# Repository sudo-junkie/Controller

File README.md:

# Controller

KiCad 7 design files (schematic, PCB, gerber, BOM) for a replacement PCB for the UCOM USB game controller that introduces the following features:
- ESP32 based (WiFi + Bluetooth onboard) with external (IPEX) antenna
- SPI LCD Connector
- Micro SD Card slot 
- Single cell lithium battery charger
- USB C for programming/joystick
- Onboard accelerometer + gyroscope + magnetometer (MPU9250)
- 8 analog inputs (4 pressure-sensitive buttons + 2 joysticks)
- 8 digital inputs
- Toggle switch
- Infrared TX/RX 
- RGB LED

While this board has been designed to be dimensionally identical to the original PCB, a little 'hacking' on the part of the casing to make room for the USB connector, infrared transmitter/receiver and for the mounting of the toggle switch and external ESP32 antenna.

- Original

- Upgraded

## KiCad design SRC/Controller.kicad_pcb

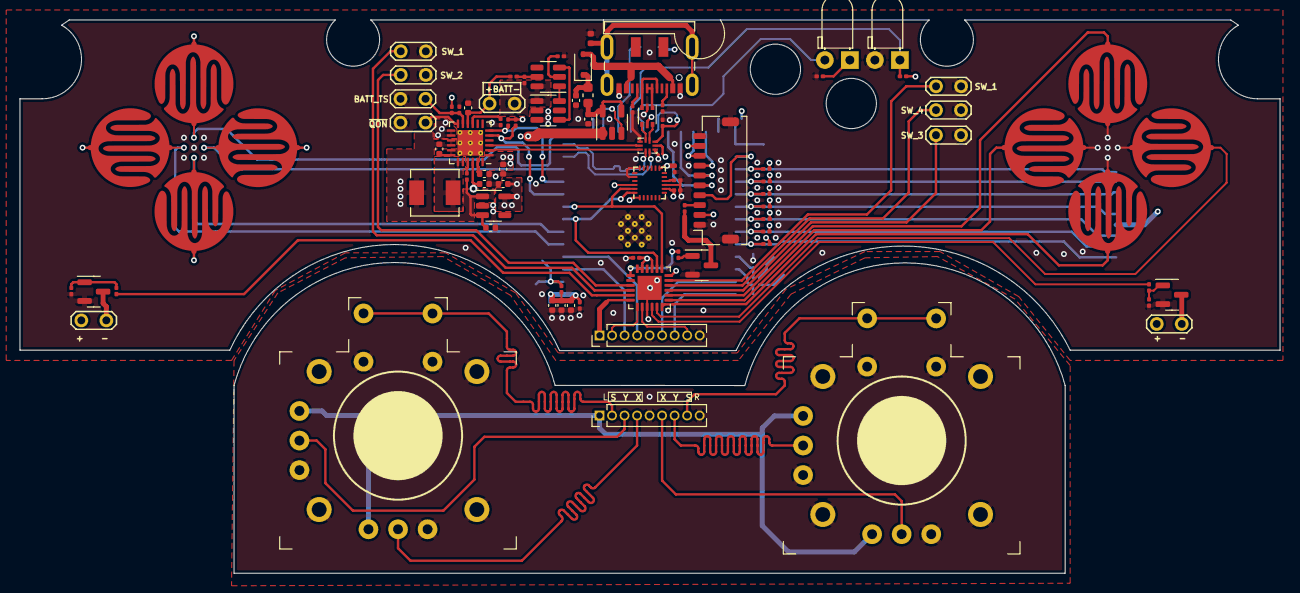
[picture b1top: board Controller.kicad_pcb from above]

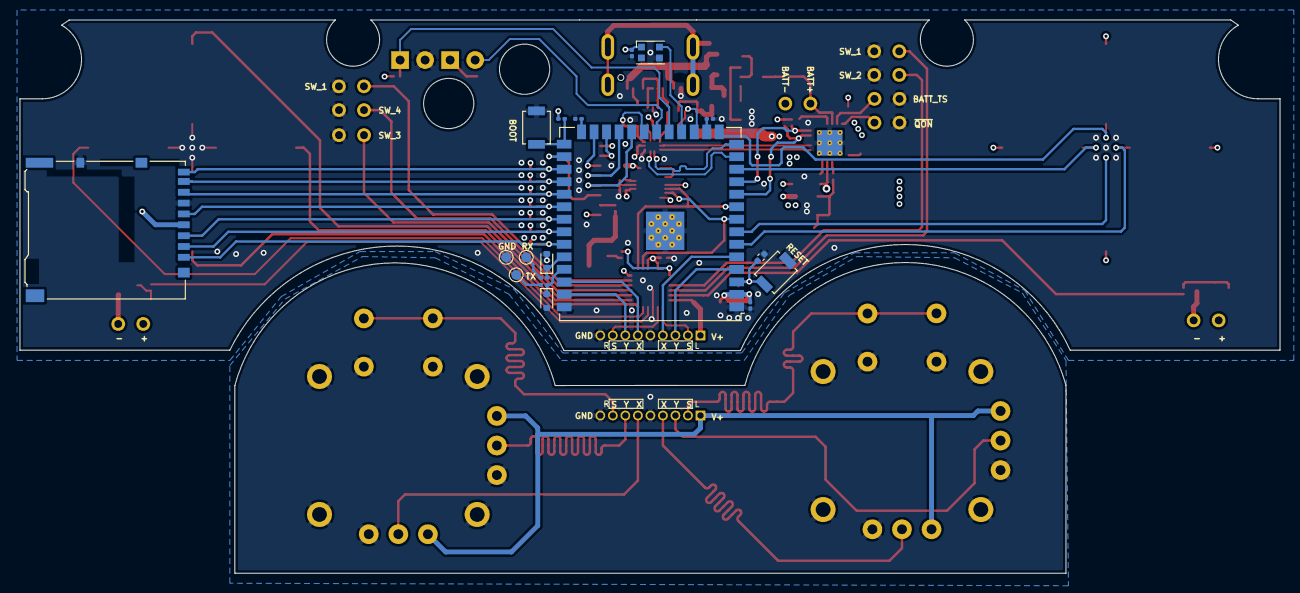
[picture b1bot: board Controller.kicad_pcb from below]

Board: 4 copper layers, 127.8 x 56.1 mm, 105 parts (18 on the bottom side), 92 nets.

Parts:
BT301: Battery_Cell; TestPoint_2Pads_Pitch2.54mm_Drill0.8mm
C201, C202, C304, C307, C308, C403, C406: 1u; C_0402_1005Metric
C301, C302, C303, C401, C402: 10u; C_0402_1005Metric
C305: 4u7; C_0402_1005Metric
C306, C404, C407, C502, C503, C505: 100n; C_0201_0603Metric
C309: 47n; C_0201_0603Metric
C405, C501: 10n; C_0201_0603Metric
D201: 3A; D_SOD-323
D401, D402: 3V3; D_SOD-523
D403: WS2812B; LED_WS2812B-2020_PLCC4_2.0x2.0mm
D501: IR204A; LED_D3.0mm_Horizontal_O1.27mm_Z2.0mm_IRGrey
FB201: 120R@100MHz 3A; L_0603_1608Metric
J101: USB_C_Receptacle_USB2.0; USB_C_Receptacle_JAE_DX07S016JA1R1500
J501: Micro_SD_Card; microSD_HC_Hirose_DM3AT-SF-PEJM5
J502: Conn_LCD; JST_SHL_SM10B-SHLS-TF_1x10-1MP_P1.00mm_Horizontal
J503, J503#2: NP; PinHeader_1x09_P1.27mm_Vertical
L101: 1u; L_0402_1005Metric
L301: 1u; L_Sunlord_MWSA0402S
M501, M502: Motor_VIB; TestPoint_2Pads_Pitch2.54mm_Drill0.8mm
Q501, Q502, Q503: MMBT3904; SOT-23
Q504: Q_Photo_NPN; LED_D3.0mm_Horizontal_O1.27mm_Z2.0mm_IRBlack
R201, R305, R306, R308, R403, R404, R405, R406, R501, R502, R503, R504, R505, R506, R507, R512, R513: 10K; R_0201_0603Metric
R202, R203, R303: 5K1; R_0201_0603Metric
R301: 100R; R_0201_0603Metric
R302, R508, R509, R510, R511, R514, R515: 1K; R_0201_0603Metric
R304: 30K9; R_0201_0603Metric
R401, R402: 470R; R_0201_0603Metric
SW301: SW_PWR; TestPoint_2Pads_Pitch2.54mm_Drill0.8mm
SW401: SW_RST; SW_SPST_B3U-1000P
SW402: SW_DWN; SW_SPST_B3U-1000P
SW501, SW502, SW503, SW504, SW510, SW511, SW512, SW513: Button_SMD; SMD_BTN
SW505: SW_DIP_x01; TestPoint_2Pads_Pitch2.54mm_Drill0.8mm
SW506, SW507, SW508, SW509: Button_SMD; TestPoint_2Pads_Pitch2.54mm_Drill0.8mm
TH301: 103AT; TestPoint_2Pads_Pitch2.54mm_Drill0.8mm
TP401: TP_TX; TestPoint_Pad_D1.0mm
TP402: TP_RX; TestPoint_Pad_D1.0mm
TP403: TP_GND; TestPoint_Pad_D1.0mm
U201: AP2171W; SOT-23-5
U202: PI3USB4000AZM; UQFN-10_1.4x1.8mm_P0.4mm
U203: USBLC6-2P6; SOT-666
U301: DW01A; SOT-23-6
U302: 8205S; SOT-23-6
U303: TLV75733PDBV; SOT-23-5
U304: BQ25611; WQFN-24-1EP_4x4mm_P0.5mm_EP2.6x2.6mm_ThermalVias
U401: ESP32-S3-WROOM-1-N16R8; ESP32-S3-WROOM-1U
U501: MPU-9250; InvenSense_QFN-24_3x3mm_P0.4mm
U502: JY1; Joystick
U503: TCA9555RTWR; WQFN-24-1EP_4x4mm_P0.5mm_EP2.45x2.45mm
U504: JY2; Joystick

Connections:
+3V3: C308.1, C401.1, C402.1, C403.1, C404.1, C405.1, C407.1, C501.1, C502.1, C503.1, D403.1 (VDD), J501.4 (VDD), J502.2, J502.9, R305.1, R306.1, R403.1, R404.1, R501.2, R502.2, R503.2, R504.2, R505.2, R506.2, R507.2, R514.1, SW501.1, SW502.1, SW503.1, SW504.1, U203.5 (VBUS), U303.5 (OUT), U401.2 (3V3), U501.1 (RESV_VDDIO), U501.8 (VDDIO), U501.13 (VDD), U501.22 (~CS), U503.18 (A0), U503.21 (VCC), U503.23 (A1), U503.24 (A2)
/Controller_Peripherals/AUX_SCL: U401.9 (IO16), U501.23 (SCL/SCLK), U503.19 (SCL)
/Controller_Peripherals/AUX_SDA: U401.8 (IO15), U501.24 (SDA/MOSI), U503.20 (SDA)
/Controller_Peripherals/IR_LED: D501.2 (A), U401.20 (IO12)
/Controller_Peripherals/IR_RECV: Q504.1 (C), R514.2, U401.19 (IO11)
/Controller_Peripherals/JYL_SW: J503.2, J503#2.2, U502.S1, U503.7 (P06)
/Controller_Peripherals/JYR_SW: J503.8, J503#2.8, U503.8 (P07), U504.S1
/Controller_Peripherals/LCD_BL: R509.1, U503.1 (P00)
/Controller_Peripherals/LCD_CK: J502.5, U401.22 (IO14)
/Controller_Peripherals/LCD_CS: J502.6, U401.23 (IO21)
/Controller_Peripherals/LCD_DI: J502.7, U401.25 (IO48)
/Controller_Peripherals/LCD_DO: J502.8, U401.24 (IO47)
/Controller_Peripherals/LCD_EN: J502.4, U401.28 (IO35)
/Controller_Peripherals/LCD_K: J502.3, R508.1
/Controller_Peripherals/REGOUT: C505.1, U501.10 (REGOUT)
/Controller_Peripherals/SD_CK: J501.5 (CLK), R505.1, U401.32 (IO39)
/Controller_Peripherals/SD_CMD: J501.3 (CMD), R506.1, U401.33 (IO40)
/Controller_Peripherals/SD_D0: J501.7 (DAT0), R501.1, U401.31 (IO38)
/Controller_Peripherals/SD_D1: J501.8 (DAT1), R502.1, U401.30 (IO37)
/Controller_Peripherals/SD_D2: J501.1 (DAT2), R503.1, U401.35 (IO42)
/Controller_Peripherals/SD_D3: J501.2 (DAT3/CD), R504.1, U401.34 (IO41)
/Controller_Peripherals/SD_DET: J501.9 (DET), R507.1, U401.29 (IO36)
/Controller_Peripherals/SW_1: SW506.1, U503.4 (P03)
/Controller_Peripherals/SW_2: SW507.1, U503.3 (P02)
/Controller_Peripherals/SW_3: SW508.1, U503.15
/Controller_Peripherals/SW_4: SW509.1, U503.16
/Controller_Peripherals/SW_DN: SW502.2, U401.7 (IO7)
/Controller_Peripherals/SW_L1: SW513.1, U503.14
/Controller_Peripherals/SW_L2: SW512.1, U503.11
/Controller_Peripherals/SW_L3: SW511.1, U503.12
/Controller_Peripherals/SW_L4: SW510.1, U503.13
/Controller_Peripherals/SW_LT: SW503.2, U401.6 (IO6)
/Controller_Peripherals/SW_RT: SW504.2, U401.12 (IO8)
/Controller_Peripherals/SW_SPST: SW505.1, U503.17
/Controller_Peripherals/SW_UP: SW501.2, U401.15 (IO3)
/Controller_Peripherals/VIB_MOT_L: R510.1, U503.10
/Controller_Peripherals/VIB_MOT_R: R511.1, U503.5 (P04)
/Controller_Peripherals/XL: J503.4, J503#2.4, U401.5 (IO5), U502.X2
/Controller_Peripherals/XR: J503.6, J503#2.6, U401.38 (IO2), U504.X2
/Controller_Peripherals/YL: J503.3, J503#2.3, U401.4 (IO4), U502.Y2
/Controller_Peripherals/YR: J503.7, J503#2.7, U401.39 (IO1), U504.Y2
/Controller_Power/BATT+: BT301.1 (+), C302.1, R301.1, U304.10 (BATSNS), U304.13 (BAT), U304.14 (BAT)
/Controller_Power/BATT-: BT301.2 (-), C306.2, U301.6 (GND), U302.1 (S1)
/Controller_Power/BQ_NCE: R308.1, U304.9 (~CE)
/Controller_Power/BQ_SCL: R306.2, U304.5 (SCL), U401.10 (IO17)
/Controller_Power/BQ_SDA: R305.2, U304.6 (SDA), U401.11 (IO18)
/Controller_Power/PMID: C301.1, U304.23 (PMID)
/Controller_Power/REGN: C305.1, R303.1, U304.22 (REGN)
/Controller_Power/SW: L301.1, U304.19 (SW), U304.20 (SW)
/Controller_Power/USB_D+: U202.5 (L0+), U304.2 (D+)
/Controller_Power/USB_D-: U202.4 (L0-), U304.3 (D-)
/Controller_Power/~QON: SW301.1, U304.12 (~QON)
/Interface_USB_C_2.0/CC1: J101.A5 (CC1), R202.1
/Interface_USB_C_2.0/CC2: J101.B5 (CC2), R203.1
/Interface_USB_C_2.0/D+: U202.1 (C0+), U203.6 (I/O1)
/Interface_USB_C_2.0/D-: U202.2 (C0-), U203.4 (I/O2)
/Interface_USB_C_2.0/USB_D1+: U202.7 (L1+), U401.13 (USB_D+)
/Interface_USB_C_2.0/USB_D1-: U202.6 (L1-), U401.14 (USB_D-)
/Interface_USB_C_2.0/USB_D+: J101.A6 (D+), J101.B6 (D+), U203.1 (I/O1)
/Interface_USB_C_2.0/USB_D-: J101.A7 (D-), J101.B7 (D-), U203.3 (I/O2)
/Interface_USB_C_2.0/USB_SEL: R201.2, U202.10 (SEL), U401.21 (IO13)
/Interface_USB_C_2.0/VBUS_IN: D201.2 (A), J101.A4 (VBUS), J101.A9 (VBUS), J101.B4 (VBUS), J101.B9 (VBUS)
/Interface_USB_C_2.0/VIN_FLG: U201.3 (~FLG), U401.17 (IO9)
/RF_MODULE_ESP32-S3-WROOM-1U/CHIP_EN: C406.1, R403.2, SW401.2, U401.3 (EN)
/RF_MODULE_ESP32-S3-WROOM-1U/ESP_RX: D402.1 (K), R402.1, U401.36 (RXD0)
/RF_MODULE_ESP32-S3-WROOM-1U/ESP_TX: D401.1 (K), R401.2, U401.37 (TXD0)
/RF_MODULE_ESP32-S3-WROOM-1U/GPIO0: R404.2, SW402.1, U401.27 (IO0)
/RF_MODULE_ESP32-S3-WROOM-1U/GPIO45: R405.2, U401.26 (IO45)
/RF_MODULE_ESP32-S3-WROOM-1U/GPIO46: R406.2, U401.16 (IO46)
/RF_MODULE_ESP32-S3-WROOM-1U/LED_RGB: D403.4 (DIN), U401.18 (IO10)
Earth: J101.S1 (SHIELD), L101.1
GND: C201.2, C202.2, C301.2, C302.2, C303.2, C304.2, C305.2, C307.2, C308.2, C401.2, C402.2, C403.2, C404.2, C405.2, C406.2, C407.2, C501.2, C502.2, C503.2, C505.2, D401.2 (A), D402.2 (A), D403.3 (VSS), J101.A1 (GND), J101.A12 (GND), J101.B1 (GND), J101.B12 (GND), J501.6 (VSS), J501.10 (SHIELD), J502.1, J502.10, J502.MP (MountPin), J503.5, J503.9, J503#2.5, J503#2.9, L101.2, Q501.2 (E), Q502.2 (E), Q503.2 (E), Q504.2 (E), R201.1, R202.2, R203.2, R302.2, R304.2, R308.2, R405.1, R406.1, R512.1, R513.1, R515.2, SW301.2, SW401.1, SW402.2, SW505.2, SW506.2, SW507.2, SW508.2, SW509.2, SW510.2, SW511.2, SW512.2, SW513.2, TH301.2, TP403.1, U201.2 (GND), U202.3 (GND), U202.8 (~EN), U203.2 (GND), U302.3 (S2), U303.2 (GND), U304.17 (GND), U304.18 (GND), U304.25 (GND), U401.1 (GND), U401.40 (GND), U401.41 (GND), U501.9 (AD0/MISO), U501.18 (GND), U501.20 (RESV_GND), U502.MP, U502.S2, U502.X3, U502.Y3, U503.9 (GND), U503.25 (EPAD), U504.MP, U504.S2, U504.X3, U504.Y3
unnamed: C201.1, D201.1 (K), FB201.1
unnamed: D501.1 (K), R515.1
unnamed: M501.2 (-), Q502.3 (C)
unnamed: M502.2 (-), Q503.3 (C)
unnamed: Q501.1 (B), R509.2
unnamed: Q501.3 (C), R508.2
unnamed: Q502.1 (B), R510.2, R512.2
unnamed: Q503.1 (B), R511.2, R513.2
unnamed: R401.1, TP401.1
unnamed: R402.2, TP402.1
unnamed: C202.1, FB201.2, U201.4 (EN), U201.5 (IN)
unnamed: R302.1, U301.2 (CS)
unnamed: U301.3 (OC), U302.4 (G2)
unnamed: U301.1 (OD), U302.6 (G1)
unnamed: C306.1, R301.2, U301.5 (VCC)
unnamed: C309.1, U304.21 (BTST)
unnamed: R303.2, R304.1, TH301.1, U304.11 (TS)
VAA: J503.1, J503#2.1, U502.X1, U502.Y1, U503.6 (P05), U504.X1, U504.Y1
VBUS: C304.1, U201.1 (OUT), U304.1 (VAC), U304.24 (VBUS)
VCC: C303.1, C307.1, C309.2, L301.2, M501.1 (+), M502.1 (+), U202.9 (VDD), U303.1 (IN), U303.3 (EN), U304.15 (SYS), U304.16 (SYS)

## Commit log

2023-10-05 Added files
2023-10-05 Edited README.md
